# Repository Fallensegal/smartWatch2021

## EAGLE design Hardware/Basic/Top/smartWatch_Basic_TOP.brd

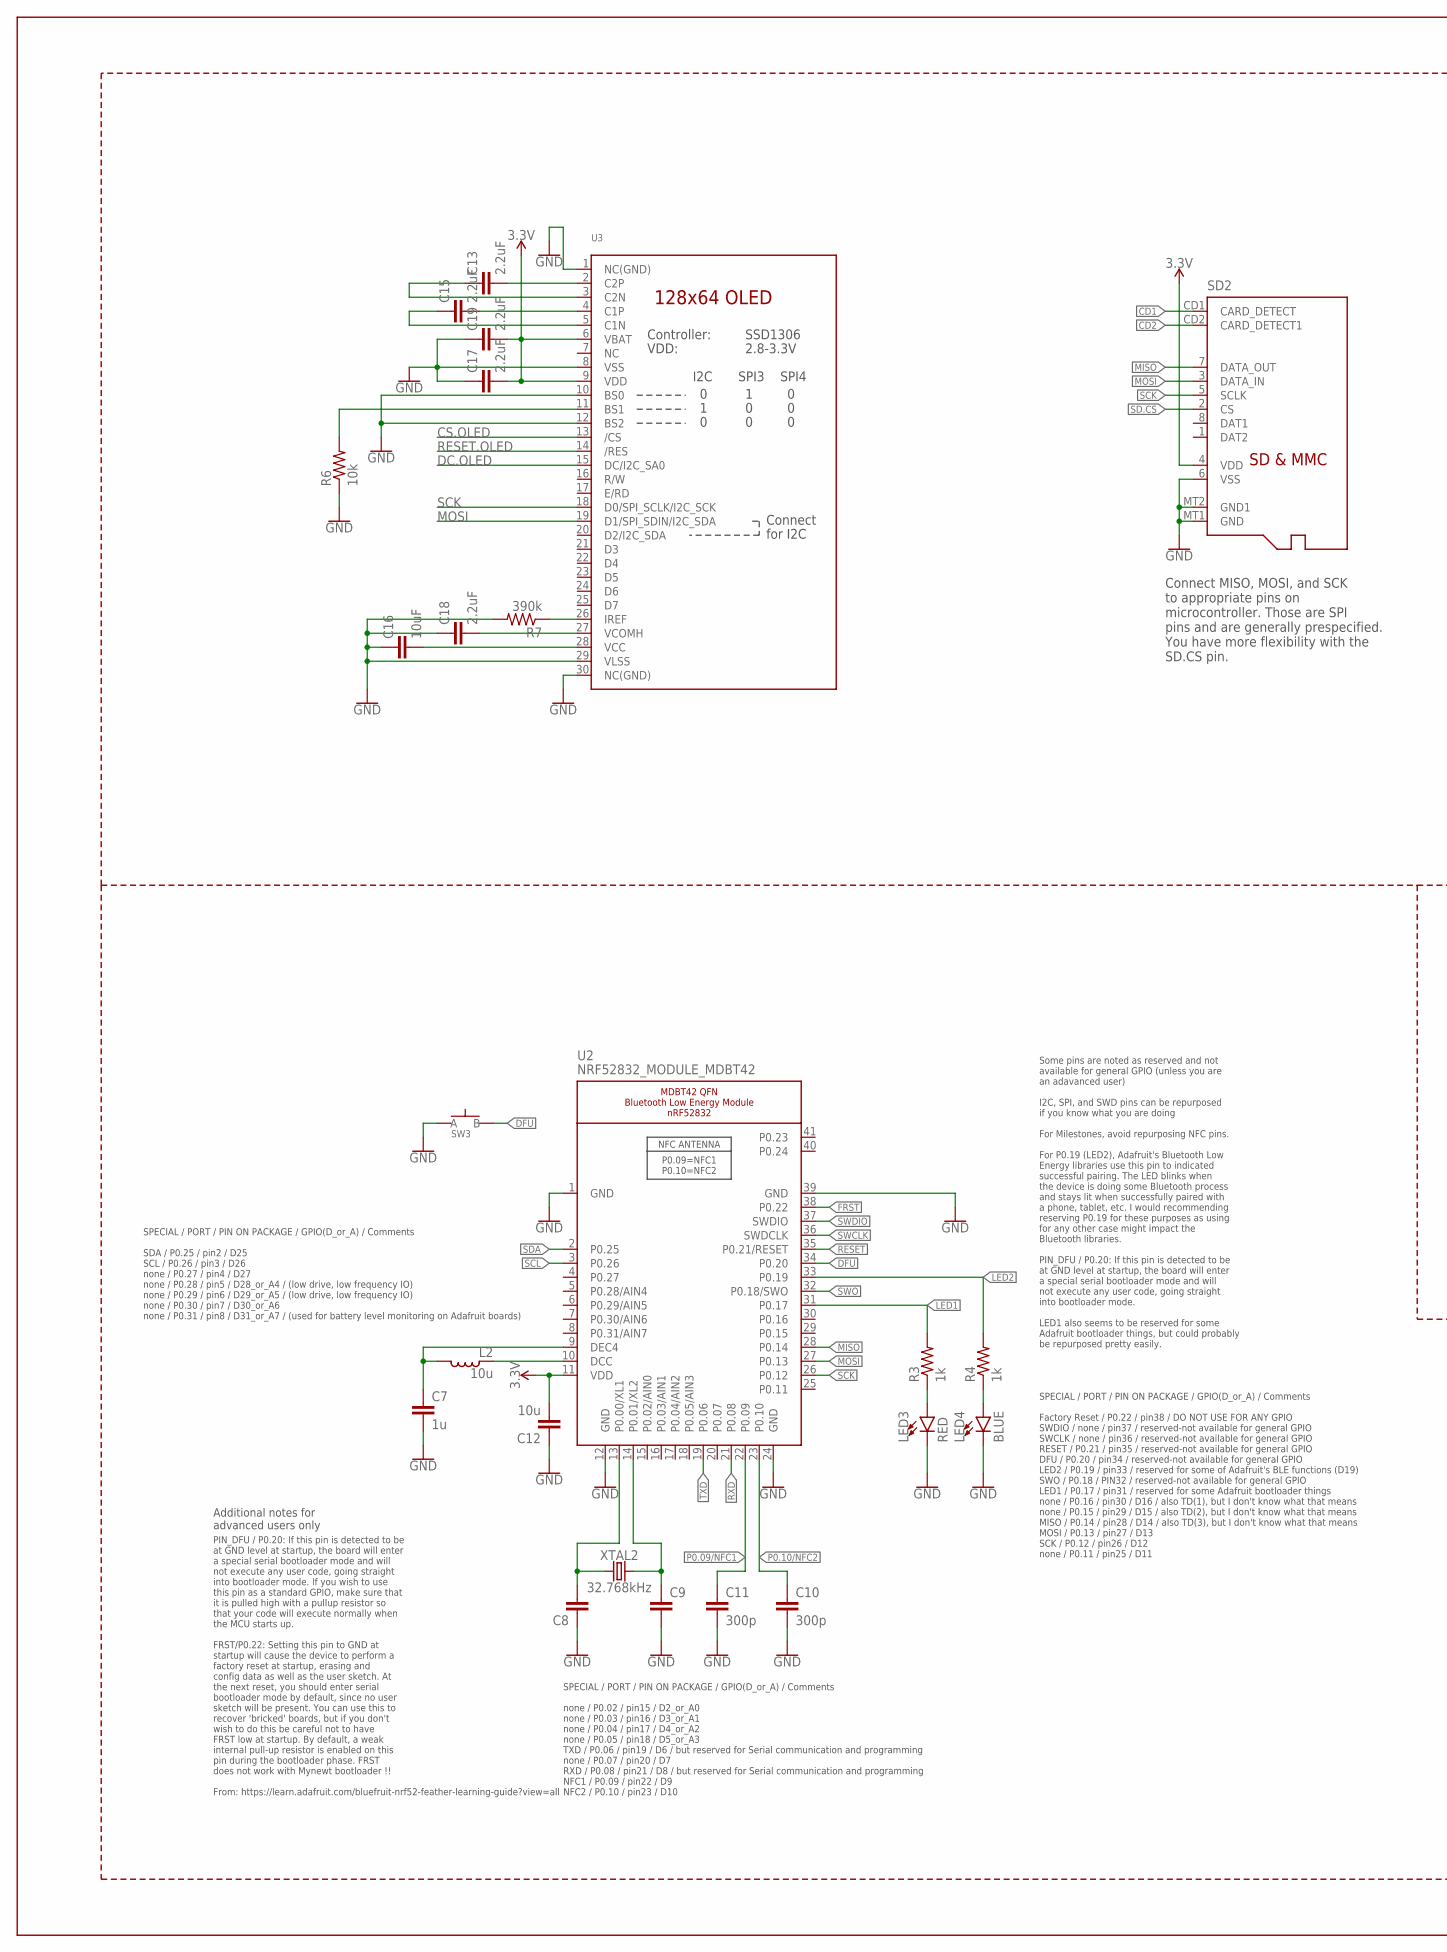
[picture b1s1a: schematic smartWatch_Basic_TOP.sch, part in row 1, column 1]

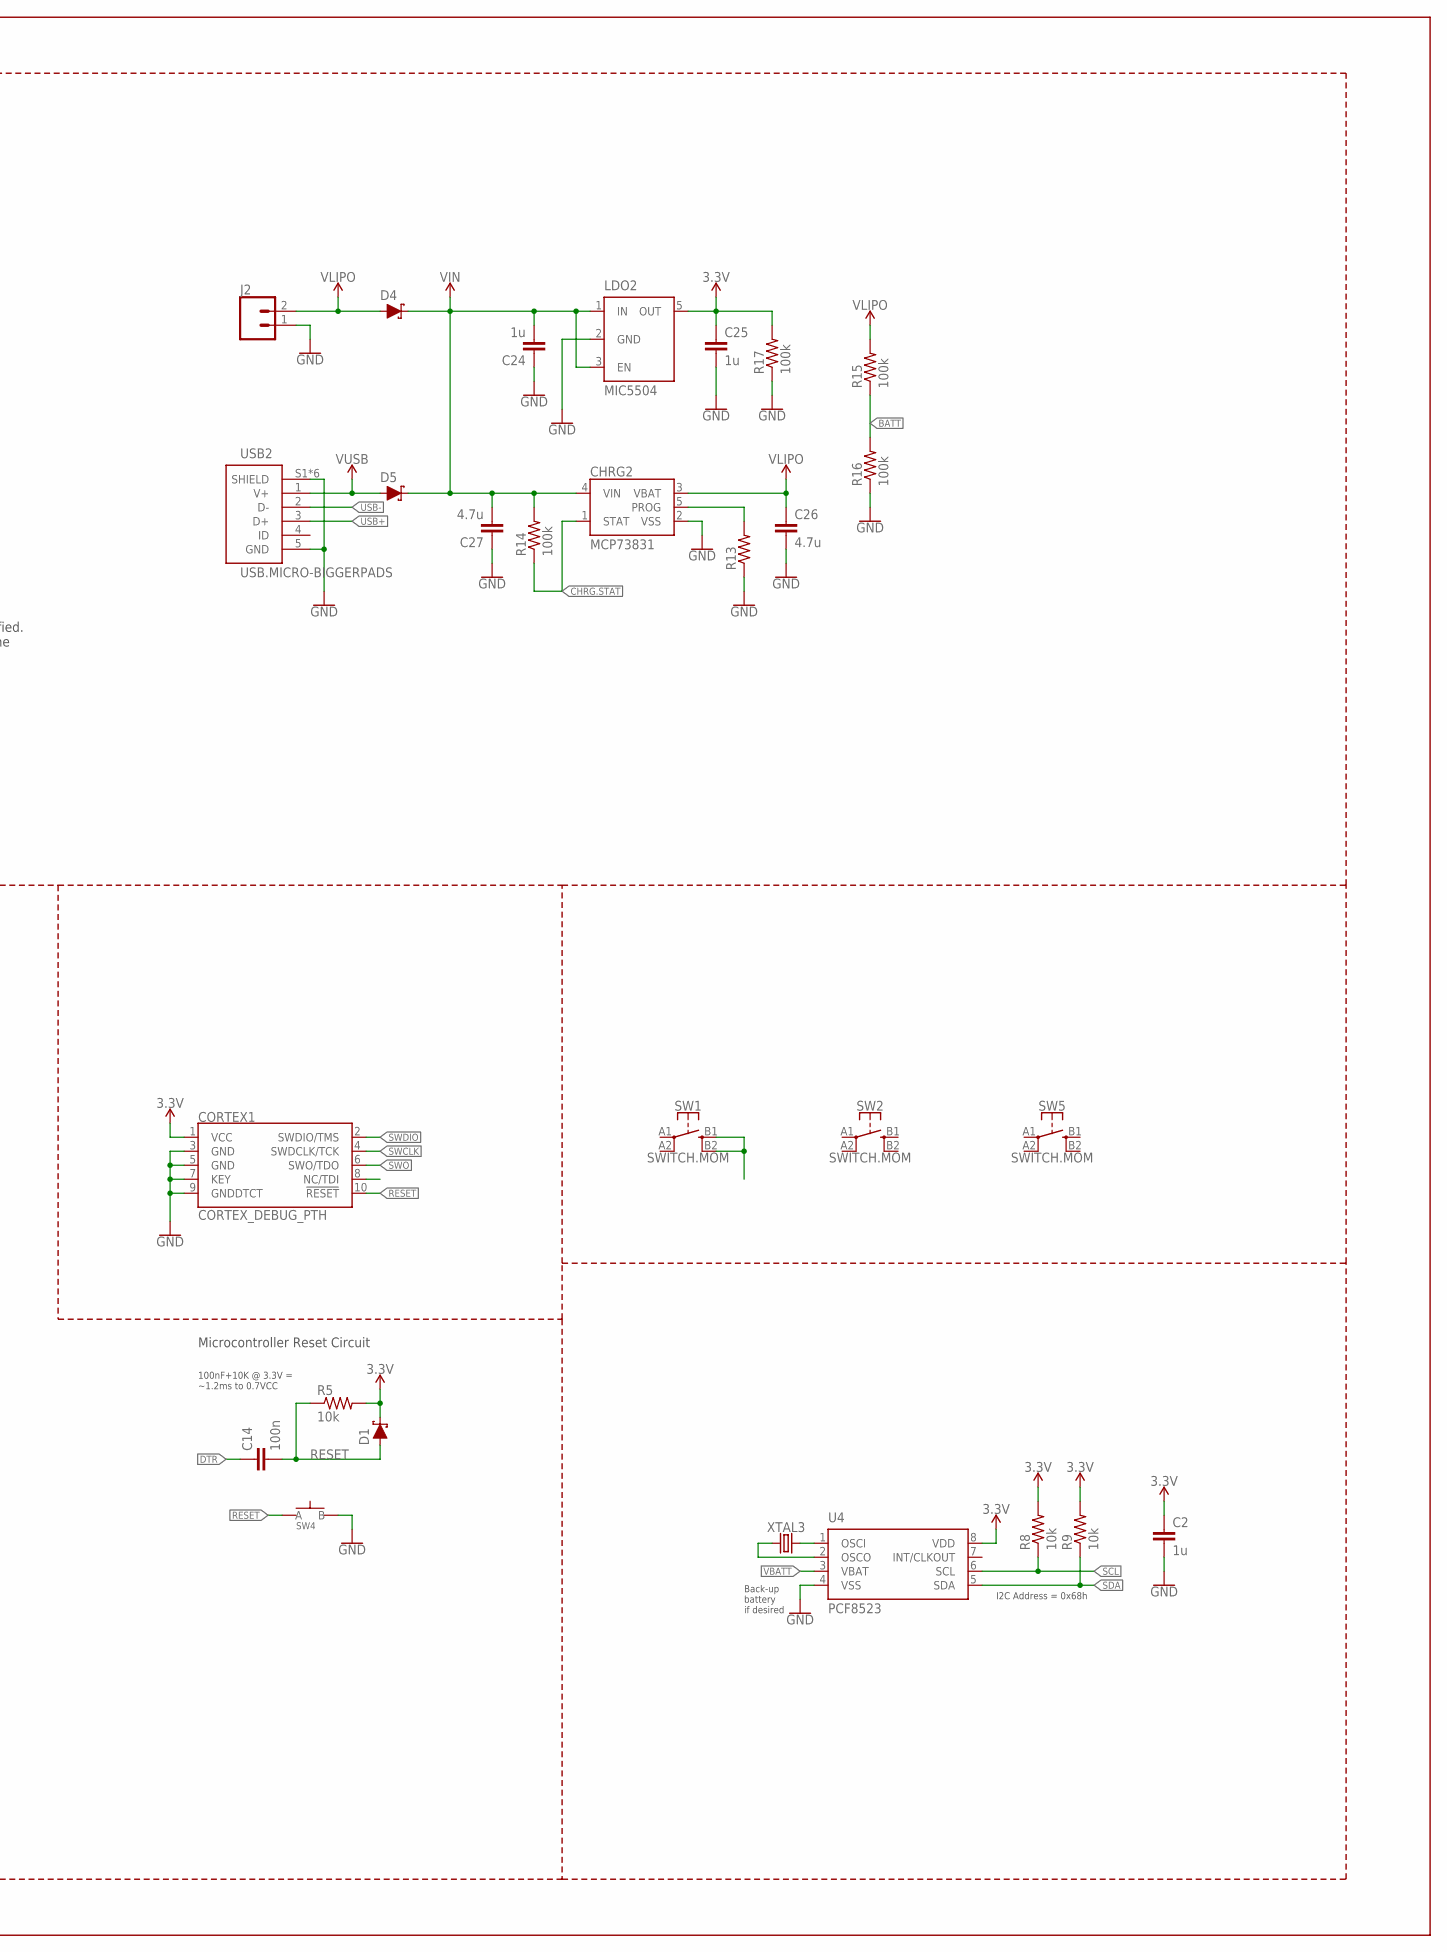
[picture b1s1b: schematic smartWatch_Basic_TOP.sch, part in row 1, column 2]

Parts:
C2, C7, C24, C25: 1u; C0603
C8, C9: CAPACITOR0603; C0603
C10, C11: 300p; C0603
C12: 10u; C0805
C13, C15, C17, C18, C19: 2.2uF; C0402
C14: 100n; C0603
C16: 10uF; C0603
C26, C27: 4.7u; C0603
CHRG2: MCP73831; SOT23-5
CORTEX1: CORTEX_DEBUG_PTH; 2X5-PTH-1.27MM
D1, D4, D5: SCHOTTKY-USC; USC
J2: CONN_02; 1X02
L2: 10u; L0603
LDO2: MIC5504; SOT23-5
LED3: RED; LED-0603
LED4: BLUE; LED-0603
R3, R4: 1k; R0603
R5, R6, R8, R9: 10k; R0603
R7: 390k; R0603
R13: RESISTOR0603; R0603
R14, R15, R16, R17: 100k; R0603
SD2: MICROSD
SW1, SW2, SW5: SWITCH.MOM; TACTILE_SWITCH_SMD_6.2MM_TALL
SW3, SW4: SPST-PTS830GG140-COPY.1-3; BUTTON-GULLWING
U2: NRF52832_MODULE_MDBT42; BLE_MODULE_RAYTAC_MDBT42
U3: DISP_OLED_UG-2864HSWEG01-NO-WRAPAROUND; UG-2864HSWEG01_0.96IN_NO-WRAPAROUND
U4: PCF8523; SO8; DIGIKEY 568-5306-1-ND
USB2: USB.MICRO-BIGGERPADS; USB-MICRO-01.BIGGERPADS
XTAL2: 32.768kHz; 2-SMD.NOLEAD.2.0MMTO1.2MM
XTAL3: 32.7680kHz; 2-SMD.NOLEAD.2.0MMTO1.2MM

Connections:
3.3V: C2.1, C12.2, C17.2, C19.2, C25.1, CORTEX1.1 (VCC), D1.- (C), LDO2.5 (OUT), R5.2, R8.2, R9.2, R17.2, SD2.4 (VDD), U2.11 (VDD), U3.6 (VBAT), U3.9 (VDD), U4.8 (VDD)
BATT: R15.1, R16.2
CD1: SD2.CD1 (CARD_DETECT)
CD2: SD2.CD2 (CARD_DETECT1)
CHRG.STAT: CHRG2.1 (STAT), R14.1
CS.OLED: U3.13 (/CS)
DC.OLED: U3.15 (DC/I2C_SA0)
DFU: SW3.3 (B), U2.34 (P0.20)
DTR: C14.1
FRST: U2.38 (P0.22)
GND: C2.2, C7.2, C8.1, C9.2, C10.2, C11.2, C12.1, C16.1, C17.1, C18.1, C19.1, C24.1, C25.2, C26.2, C27.1, CHRG2.2 (VSS), CORTEX1.3 (GND), CORTEX1.5 (GND), CORTEX1.7 (KEY), CORTEX1.9 (GNDDTCT), J2.1, LDO2.2 (GND), LED3.C, LED4.C, R6.1, R7.2, R13.1, R16.1, R17.1, SD2.6 (VSS), SD2.MT1 (GND), SD2.MT2 (GND1), SW3.1 (A), SW4.3 (B), U2.1 (GND), U2.12 (GND), U2.24 (GND), U2.39 (GND), U3.1 (NC(GND)), U3.8 (VSS), U3.10 (BS0), U3.12 (BS2), U3.29 (VLSS), U3.30 (NC(GND)), U4.4 (VSS), USB2.5 (GND), USB2.S1 (SHIELD), USB2.S2 (SHIELD), USB2.S3 (SHIELD), USB2.S4 (SHIELD), USB2.S5 (SHIELD), USB2.S6 (SHIELD)
LED1: R3.2, U2.31 (P0.17)
LED2: R4.2, U2.33 (P0.19)
MISO: SD2.7 (DATA_OUT), U2.28 (P0.14)
MOSI: SD2.3 (DATA_IN), U2.27 (P0.13), U3.19 (D1/SPI_SDIN/I2C_SDA)
unnamed: R6.2, U3.11 (BS1)
unnamed: R7.1, U3.26 (IREF)
unnamed: C13.2, U3.2 (C2P)
unnamed: C8.2, U2.13 (P0.00/XL1), XTAL2.P$1 (1)
unnamed: C13.1, U3.3 (C2N)
unnamed: C9.1, U2.14 (P0.01/XL2), XTAL2.P$2 (2)
unnamed: C15.2, U3.4 (C1P)
unnamed: C15.1, U3.5 (C1N)
unnamed: LED3.A, R3.1
unnamed: LED4.A, R4.1
unnamed: L2.1, U2.10 (DCC)
unnamed: C7.1, L2.2, U2.9 (DEC4)
unnamed: C16.2, U3.28 (VCC)
unnamed: C18.2, U3.27 (VCOMH)
unnamed: CHRG2.5 (PROG), R13.2
unnamed: U4.2 (OSCO), XTAL3.P$1 (1)
unnamed: U4.1 (OSCI), XTAL3.P$2 (2)
unnamed: SW1.B1 (3), SW1.B2 (4)
P0.09/NFC1: C11.1, U2.22 (P0.09)
P0.10/NFC2: C10.1, U2.23 (P0.10)
RESET: C14.2, CORTEX1.10 (!RESET), D1.+ (A), R5.1, SW4.1 (A), U2.35 (P0.21/RESET)
RESET.OLED: U3.14 (/RES)
RXD: U2.21 (P0.08)
SCK: SD2.5 (SCLK), U2.26 (P0.12), U3.18 (D0/SPI_SCLK/I2C_SCK)
SCL: R8.1, U2.3 (P0.26), U4.6 (SCL)
SD.CS: SD2.2 (CS)
SDA: R9.1, U2.2 (P0.25), U4.5 (SDA)
SWCLK: CORTEX1.4 (SWDCLK/TCK), U2.36 (SWDCLK)
SWDIO: CORTEX1.2 (SWDIO/TMS), U2.37 (SWDIO)
SWO: CORTEX1.6 (SWO/TDO), U2.32 (P0.18/SWO)
TXD: U2.19 (P0.06)
USB+: USB2.3 (D+)
USB-: USB2.2 (D-)
VBATT: U4.3 (VBAT)
VIN: C24.2, C27.2, CHRG2.4 (VIN), D4.- (C), D5.- (C), LDO2.1 (IN), LDO2.3 (EN), R14.2
VLIPO: C26.1, CHRG2.3 (VBAT), D4.+ (A), J2.2, R15.2
V_USB: D5.+ (A), USB2.1 (V+)

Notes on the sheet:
Microcontroller Reset Circuit
100nF+10K @ 3.3V = ~1.2ms to 0.7VCC
SPECIAL / PORT / PIN ON PACKAGE / GPIO(D_or_A) / Comments SDA / P0.25 / pin2 / D25 SCL / P0.26 / pin3 / D26 none / P0.27 / pin4 / D27 none / P0.28 / pin5 / D28_or_A4 / (low drive, low frequency IO) none / P0.29 / pin6 / D29_or_A5 / (low drive, low frequency IO) none / P0.30 / pin7 / D30_or_A6 none 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
SPECIAL / PORT / PIN ON PACKAGE / GPIO(D_or_A) / Comments none / P0.02 / pin15 / D2_or_A0 none / P0.03 / pin16 / D3_or_A1 none / P0.04 / pin17 / D4_or_A2 none / P0.05 / pin18 / D5_or_A3 TXD / P0.06 / pin19 / D6 / but reserved for Serial communication and programming none / P0.07 / pin20 / D7 RXD / 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
SPECIAL / PORT / PIN ON PACKAGE / GPIO(D_or_A) / Comments Factory Reset / P0.22 / pin38 / DO NOT USE FOR ANY GPIO SWDIO / none / pin37 / reserved-not available for general GPIO SWCLK / none / pin36 / reserved-not available for general GPIO RESET / P0.21 / pin35 / reserved-not available for general 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
Some pins are noted as reserved and not available for general GPIO (unless you are an adavanced user) I2C, SPI, and SWD pins can be repurposed if you know what you are doing For Milestones, avoid repurposing NFC pins. For P0.19 (LED2), Adafruit's Bluetooth Low Energy libraries use this pin to indic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
PIN_DFU / P0.20: If this pin is detected to be at GND level at startup, the board will enter a special serial bootloader mode and will not execute any user code, going straight into bootloader mode. If you wish to use this pin as a standard GPIO, make sure that it is pulled high with a pullup resis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
Additional notes for advanced users only
Connect MISO, MOSI, and SCK to appropriate pins on microcontroller. Those are SPI pins and are generally prespecified. You have more flexibility with the SD.CS pin.
I2C Address = 0x68h
Back-up battery if desired

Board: 2 copper layers, 52 parts (15 on the bottom side), 39 nets, no tracks yet.

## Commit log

2021-02-06 feature List
2021-02-06 Update Repo Structure
2021-02-07 Fixed Bad sch/brd File
2021-02-07 Fixed BOM Files
2021-02-13 Update SCH/BRD File Top
